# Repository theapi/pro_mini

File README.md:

# pro_mini
Cut down version of the Arduino Pro Min with i2C on the breadboard headers

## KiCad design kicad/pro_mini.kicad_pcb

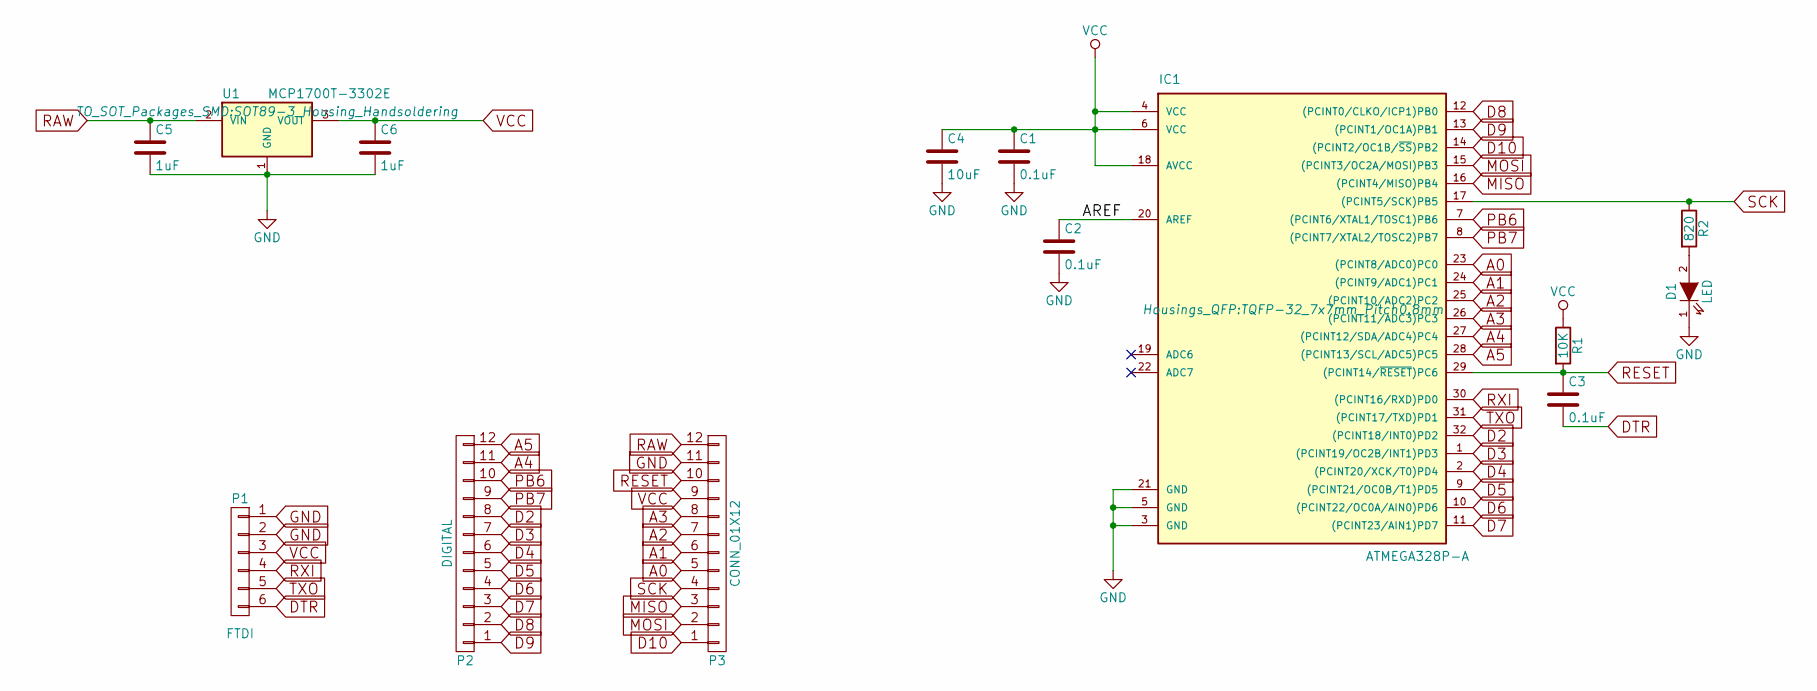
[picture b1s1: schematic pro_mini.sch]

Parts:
C1, C2, C3: 0.1uF; C_0805_HandSoldering
C4: 10uF; C_0805_HandSoldering
C5, C6: 1uF; C_0805_HandSoldering
D1: LED; LED_0805
IC1: ATMEGA328P-A; TQFP-32_7x7mm_Pitch0.8mm
P1: FTDI; Socket_Strip_Straight_1x06
P2: DIGITAL; Pin_Header_Straight_1x12
P3: CONN_01X12; Pin_Header_Straight_1x12
R1: 10K; R_0805_HandSoldering
R2: 820; R_0805_HandSoldering
U1: MCP1700T-3302E; SOT89-3_Housing_Handsoldering

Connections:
/AREF: C2.1, IC1.20 (AREF)
A0: IC1.23 ((PCINT8/ADC0)PC0), P3.5
A1: IC1.24 ((PCINT9/ADC1)PC1), P3.6
A2: IC1.25 ((PCINT10/ADC2)PC2), P3.7
A3: IC1.26 ((PCINT11/ADC3)PC3), P3.8
A4: IC1.27 ((PCINT12/SDA/ADC4)PC4), P2.11
A5: IC1.28 ((PCINT13/SCL/ADC5)PC5), P2.12
D2: IC1.32 ((PCINT18/INT0)PD2), P2.8
D3: IC1.1 ((PCINT19/OC2B/INT1)PD3), P2.7
D4: IC1.2 ((PCINT20/XCK/T0)PD4), P2.6
D5: IC1.9 ((PCINT21/OC0B/T1)PD5), P2.5
D6: IC1.10 ((PCINT22/OC0A/AIN0)PD6), P2.4
D7: IC1.11 ((PCINT23/AIN1)PD7), P2.3
D8: IC1.12 ((PCINT0/CLKO/ICP1)PB0), P2.2
D9: IC1.13 ((PCINT1/OC1A)PB1), P2.1
D10: IC1.14 ((PCINT2/OC1B/~SS~)PB2), P3.1
DTR: C3.2, P1.6
GND: C1.2, C2.2, C4.2, C5.2, C6.2, D1.1 (K), IC1.3 (GND), IC1.5 (GND), IC1.21 (GND), P1.1, P1.2, P3.11, U1.1 (GND)
MISO: IC1.16 ((PCINT4/MISO)PB4), P3.3
MOSI: IC1.15 ((PCINT3/OC2A/MOSI)PB3), P3.2
unnamed: D1.2 (A), R2.2
PB6: IC1.7 ((PCINT6/XTAL1/TOSC1)PB6), P2.10
PB7: IC1.8 ((PCINT7/XTAL2/TOSC2)PB7), P2.9
RAW: C5.1, P3.12, U1.2 (VIN)
RESET: C3.1, IC1.29 ((PCINT14/~RESET~)PC6), P3.10, R1.2
RXI: IC1.30 ((PCINT16/RXD)PD0), P1.4
SCK: IC1.17 ((PCINT5/SCK)PB5), P3.4, R2.1
TXO: IC1.31 ((PCINT17/TXD)PD1), P1.5
VCC: C1.1, C4.1, C6.1, IC1.4 (VCC), IC1.6 (VCC), IC1.18 (AVCC), P1.3, P3.9, R1.1, U1.3 (VOUT)

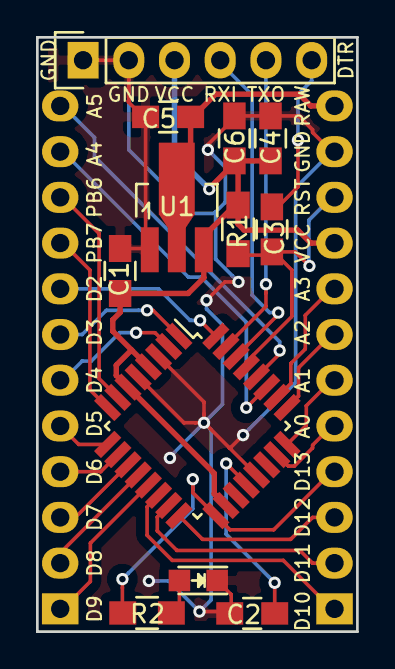
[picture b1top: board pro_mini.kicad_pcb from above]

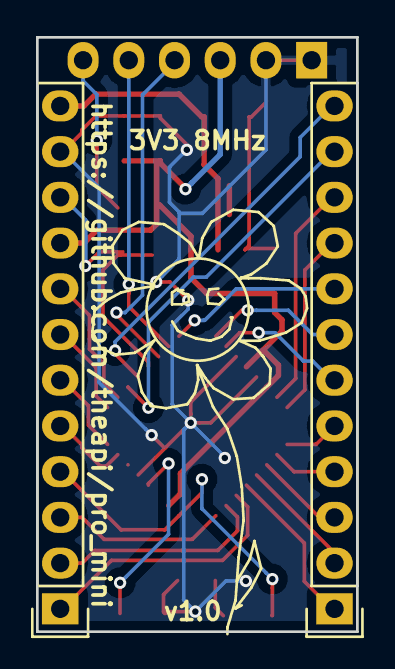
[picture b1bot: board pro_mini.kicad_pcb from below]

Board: 2 copper layers, 17.8 x 33.0 mm, 14 parts (2 on the bottom side), 29 nets.

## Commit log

2016-05-14 Same licence as original Arduino Pro Mini
2016-05-14 Original Arduino docs
2016-05-14 Start of layout
2016-05-14 LDO datasheet
2016-05-14 Layout
2016-05-14 Room for pin labels
2016-05-14 Pin labels
2016-05-14 Theapi tiny logo
2016-05-14 gerber settings
2016-05-15 Back silkscreen
2016-05-15 Optional external oscillator & reset restored to side header
